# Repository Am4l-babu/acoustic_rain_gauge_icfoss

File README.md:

# 🌧️ ICFOSS Acoustic Rain Gauge

An innovative research and development project by **ICFOSS (International Centre for Free and Open Source Software, Kerala)** to estimate rainfall rate and precipitation dynamics in real-time by analyzing the **sound of raindrops** falling on a metallic enclosure using Machine Learning.

> [!NOTE]  
> Traditional rain gauges are mechanical (tipping buckets) or optical, which require high maintenance and are prone to debris clogging. The acoustic rain gauge presents a low-cost, solid-state, maintenance-free alternative.

---

## 🛠️ Hardware & Data Acquisition (DAQ) Stack

The system consists of a recording setup calibrated against a physical mechanical reference:

1.  **Acoustic Sensor**: USB Microphone (Jieli Technology UACDemoV1.0) placed inside a specialized metallic enclosure.
2.  **Data Logger**: Raspberry Pi running automated audio acquisition scripts.
3.  **Reference Sensor**: **Davis AeroCone 6466M Rain Gauge** (mechanical tipping bucket) used for continuous calibration and ground-truth labels.

---

## 📂 Project Structure

```directory
├── software/
│   ├── rainfall_monitor_nonmechanical/
│   │   ├── model_pipeline.py       # <-- End-to-end alignment & ML pipeline
│   │   ├── demo_app.py             # Streamlit visualization dashboard
│   │   ├── raindrop_counter.py     # Real-time rain drop counting script
│   │   └── requirements.txt        # Python dependencies
│   ├── Firmware/                   # LoRaWAN and Arduino firmware
│   └── hardware/                   # Circuit diagrams & CAD drawings
├── DATA/                           # Local calibration data
├── experiments/                    # Model validation records
└── README.md                       # Root documentation
```

---

## 🧠 Machine Learning Pipeline

The pipeline aligns audio files with the mechanical sensor log, extracts acoustic features, and trains regressors to estimate rainfall.

### 1. Data Alignment
Since the mechanical Davis rain gauge reports precipitation accumulated over 3-minute windows, the pipeline parses the timestamps of 3.12-second audio clips (`yyyy_mm_dd_hh_mm_ss_micro.wav`) and groups/concatenates the 18 audio clips that fall into each 3-minute reporting window.

### 2. Acoustic Feature Extraction
For each aligned 3-minute window, we extract a **264-dimensional feature vector**:
*   **Mel-Frequency Spectrogram (64 bins)**: We compute the log Mel spectrogram and extract the **Mean** and **Standard Deviation** for each bin to represent pitch profile and loudness.
*   **Zero Crossing Rate (ZCR)**: Captures the rate of waveform sign changes to identify high-frequency drop impacts.
*   **RMS Energy**: Measures average sound amplitude (physical loudness).
*   **Spectral Centroid & Rolloff**: Identifies the center of spectral mass and skewness to differentiate rain from wind or traffic noise.

### 3. Model Performance Comparison
Models are split chronologically (75% train, 25% test) to mimic real-world deployment. The results:

| Model | Test MAE (mm) | Test RMSE (mm) | Test Correlation (Pearson $r$) |
| :--- | :---: | :---: | :---: |
| **Baseline (Mean)** | 0.7713 | 1.4733 | 0.00% |
| **Random Forest** | 0.9184 | 1.8899 | **50.23%** |
| **Gradient Boosting** | 0.8822 | 1.7740 | **49.92%** |
| **Neural Network (MLP)** | 0.9654 | 1.6861 | 36.00% |

> [!TIP]
> **Random Forest** and **Gradient Boosting** are the best performing models, achieving a **~50% correlation** with actual physical tipping events, demonstrating the viability of acoustic rainfall monitoring.

---

## 🚀 Getting Started

### 📋 Prerequisites
*   Python 3.11+ (tested on Python 3.14)
*   Virtual environment manager

### 🔧 Setup & Virtualenv
1. Clone the repository and navigate to the software folder:
   ```bash
   git clone https://github.com/Am4l-babu/acoustic_rain_gauge_icfoss.git
   cd acoustic_rain_gauge_icfoss
   ```
2. Initialize virtual environment and install dependencies:
   ```bash
   python -m venv .venv
   .venv\Scripts\activate      # On Windows
   source .venv/bin/activate   # On Unix/macOS
   pip install -r software/rainfall_monitor_nonmechanical/requirements.txt
   pip install tabulate
   ```

### ⚡ Running the Pipeline
Run the model pipeline script to align datasets, cache features, and train the regressors:
```bash
python software/rainfall_monitor_nonmechanical/model_pipeline.py
```

### 🖥️ Streamlit Dashboard
Launch the visualization dashboard to view predictions and live estimation:
```bash
streamlit run software/rainfall_monitor_nonmechanical/demo_app.py
```

---

## 👤 Developer & Contributor
*   **Amal Babu** ([@Am4l-babu](https://github.com/Am4l-babu))

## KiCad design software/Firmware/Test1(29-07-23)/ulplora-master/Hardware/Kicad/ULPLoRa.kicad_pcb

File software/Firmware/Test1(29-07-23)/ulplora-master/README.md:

# ULPLoRa Project

Ultra Low Power LoRa Board repository contains software, hardware sources and documentation
## Getting Started

* Make sure that you have a ULP LoRa Board.
* Install arduino-lmic from [here](https://gitlab.com/icfoss/OpenIoT/ulplora/tree/master/Software/Arduino/Libraries/) . Copy the library to ~/Arduino/libraries/
* Select board : Arduino Pro Mini 3.3v 8Mhz
* Try Example : [ULPLoRa_ABP](https://gitlab.com/icfoss/OpenIoT/ulplora/tree/master/Software/Arduino/Examples)
   
### Prerequisites

Arduino IDE - 1.8.5 [Tested]

## Contributing

Instructions coming up soon.

## License

This project is licensed under the MIT License - see the [LICENSE.md](LICENSE.md) file for details

## Acknowledgments

* LMIC by [matthijskooijman](https://github.com/matthijskooijman/arduino-lmic)

## Changelog

* V2.1 : Removed Onboard Li-ion charging circuit. Added reverse polarity protection for RP-604. Updated battery voltage sensing circuit. Removed analog interfaces which were found to be of limited use.

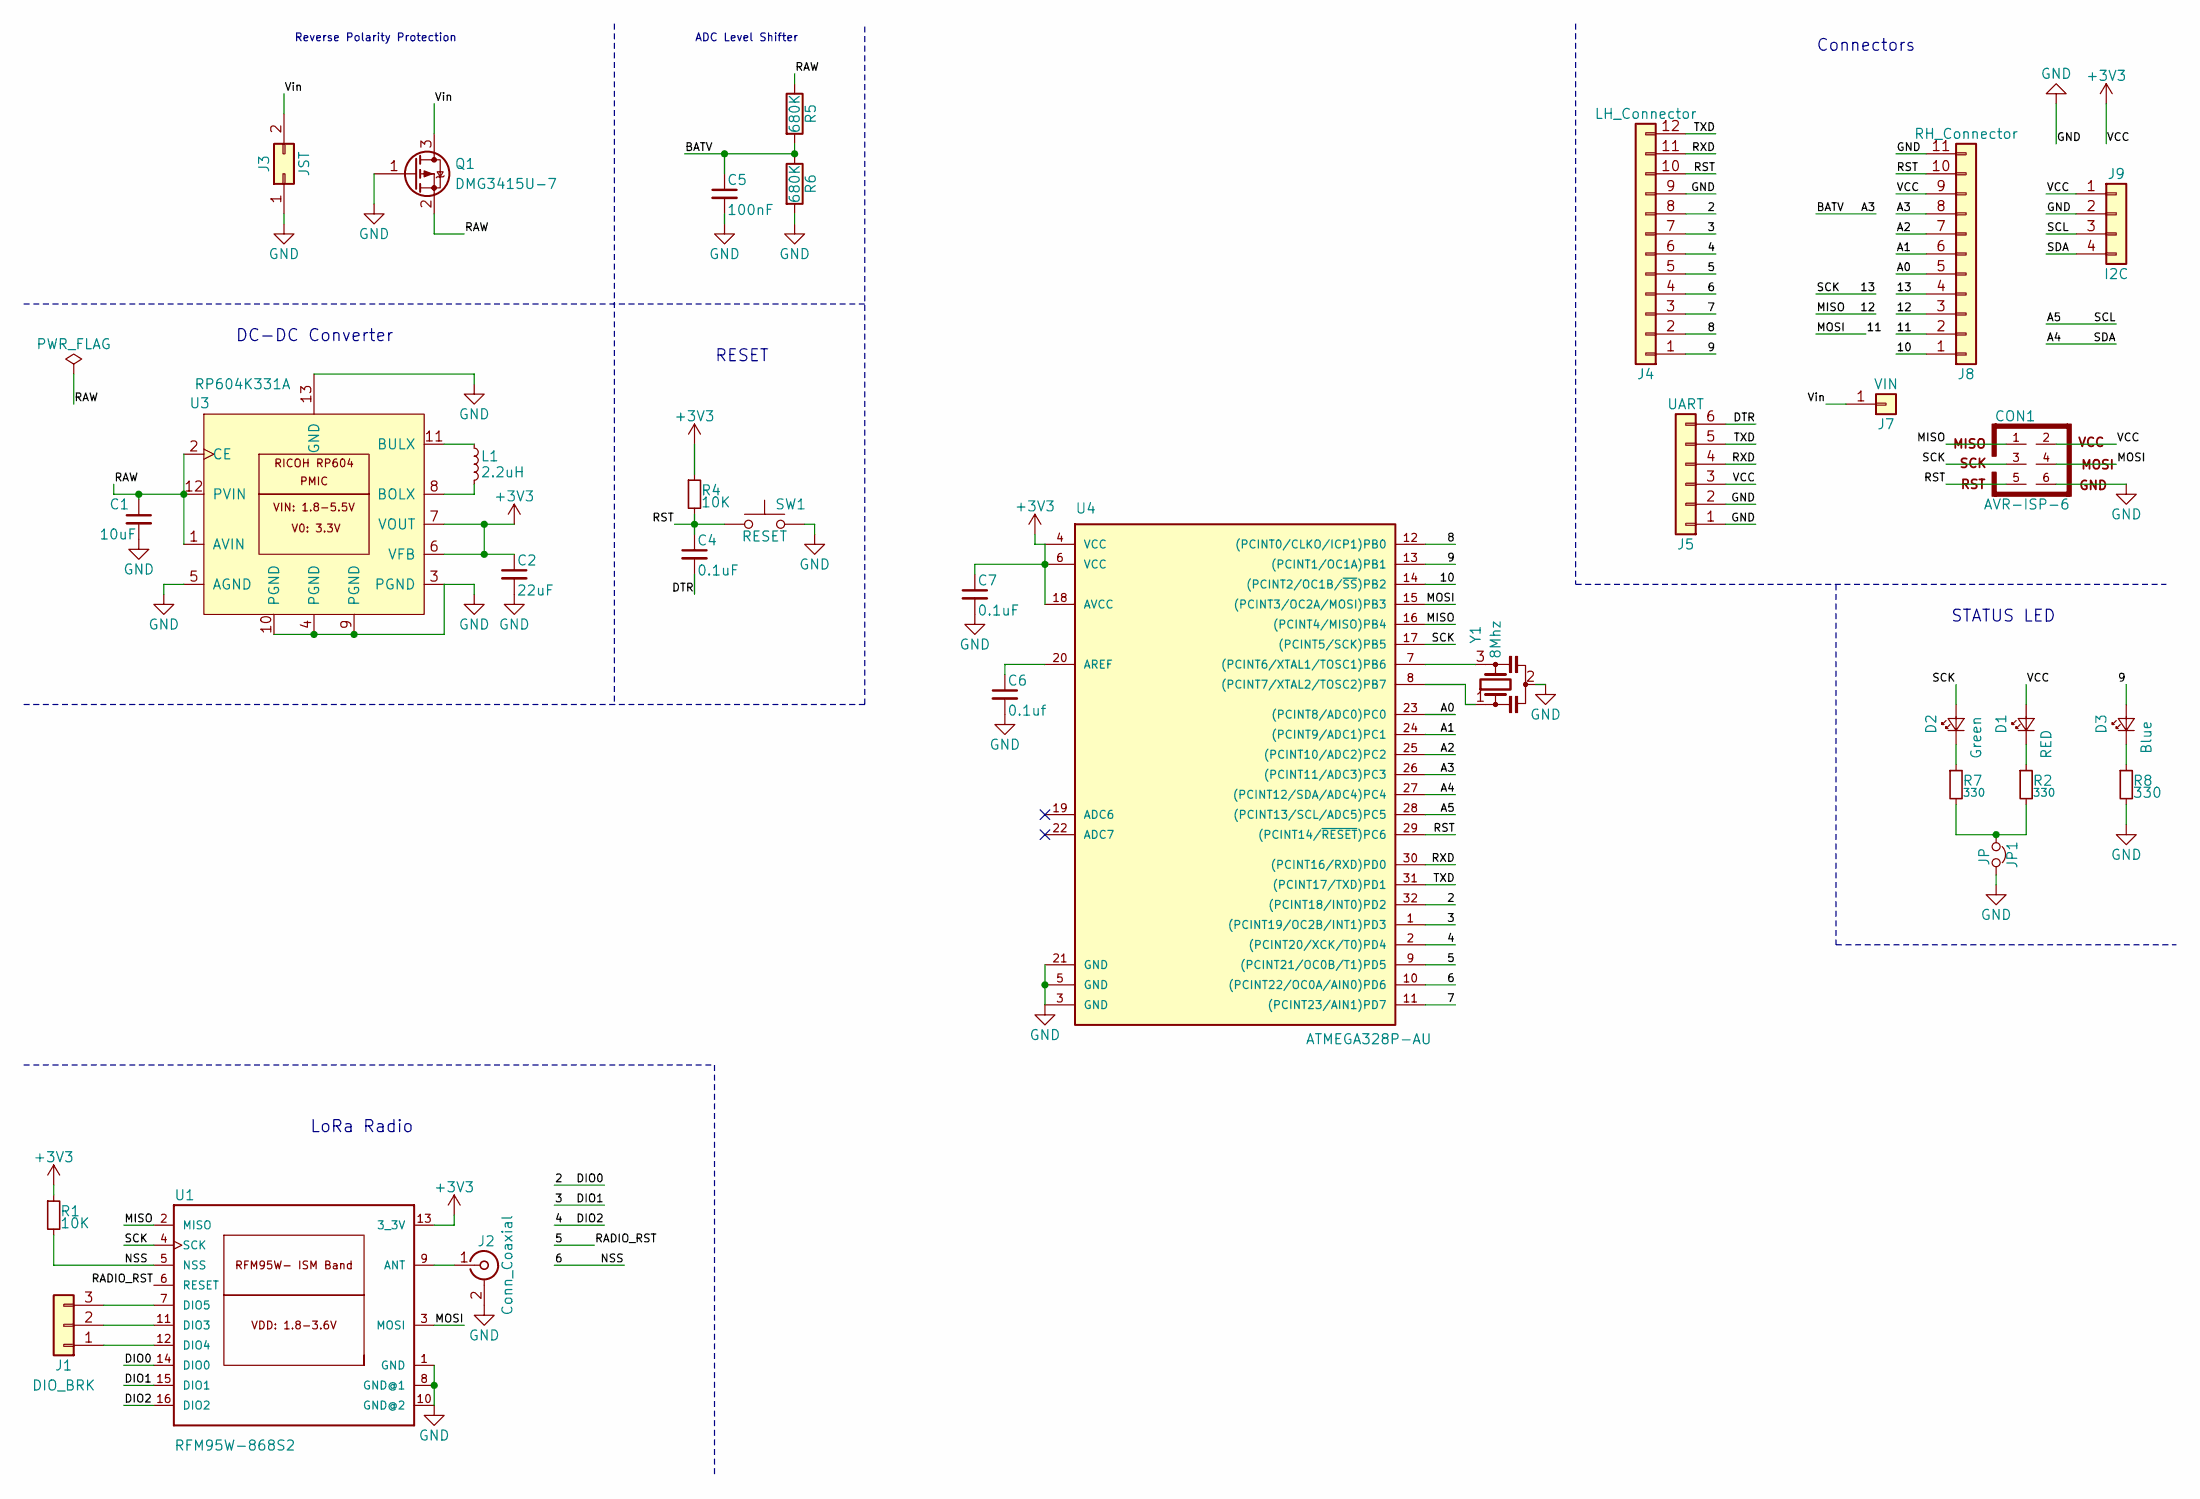
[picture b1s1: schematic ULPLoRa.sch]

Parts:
C1: 10uF; C_0805
C2: 22uF; C_0805
C4, C7: 0.1uF; C_0805
C5: 100nF; C_0805
C6: 0.1uf; C_0805
CON1: AVR-ISP-6; Pin_Header_Straight_2x03_Pitch2.54mm
D1: RED; LED_0805
D2: Green; LED_0805
D3: Blue; LED_0805
J1: DIO_BRK; Pin_Header_Straight_1x03_Pitch2.54mm
J2: Conn_Coaxial; U.FL-COAX
J3: JST; JST_PH_S2B-PH-K_02x2.00mm_Angled
J4: LH_Connector; Pin_Header_Straight_1x12_Pitch2.54mm
J5: UART; Pin_Header_Straight_1x06_Pitch2.54mm
J7: VIN; Pin_Header_Straight_1x01_Pitch2.54mm
J8: RH_Connector; Pin_Header_Straight_1x11_Pitch2.54mm
J9: I2C; JST_XH_B04B-XH-A_04x2.50mm_Straight
JP1: JP; Pin_Header_Straight_1x02_Pitch2.54mm
L1: 2.2uH; L_1210_HandSoldering
Q1: DMG3415U-7; SOT-23
R1, R4: 10K; R_0805
R2, R7, R8: 330; R_0805
R5, R6: 680K; R_0805
SW1: RESET; 3x6x2.5mm_tact_switch
U1: RFM95W-868S2; XCVR_RFM95W-868S2
U3: RP604K331A; DFN-12-1EP_2.7x3mm_Pitch0.5mm
U4: ATMEGA328P-AU; TQFP-32_7x7mm_Pitch0.8mm
Y1: 8Mhz; RESONATOR-SMD

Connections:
+3V3: C2.1, C7.1, CON1.2, D1.2 (A), J5.3, J8.9, J9.1, R1.1, R4.1, U1.13 (3_3V), U3.6 (VFB), U3.7 (VOUT), U4.4 (VCC), U4.6 (VCC), U4.18 (AVCC)
/2: J4.8, U1.14 (DIO0), U4.32 ((PCINT18/INT0)PD2)
/3: J4.7, U1.15 (DIO1), U4.1 ((PCINT19/OC2B/INT1)PD3)
/4: J4.6, U1.16 (DIO2), U4.2 ((PCINT20/XCK/T0)PD4)
/5: J4.5, U1.6 (RESET), U4.9 ((PCINT21/OC0B/T1)PD5)
/6: J4.4, R1.2, U1.5 (NSS), U4.10 ((PCINT22/OC0A/AIN0)PD6)
/7: J4.3, U4.11 ((PCINT23/AIN1)PD7)
/8: J4.2, U4.12 ((PCINT0/CLKO/ICP1)PB0)
/9: D3.2 (A), J4.1, U4.13 ((PCINT1/OC1A)PB1)
/10: J8.1, U4.14 ((PCINT2/OC1B/~SS~)PB2)
/11: CON1.4, J8.2, U1.3 (MOSI), U4.15 ((PCINT3/OC2A/MOSI)PB3)
/12: CON1.1, J8.3, U1.2 (MISO), U4.16 ((PCINT4/MISO)PB4)
/13: CON1.3, D2.2 (A), J8.4, U1.4 (SCK), U4.17 ((PCINT5/SCK)PB5)
/A0: J8.5, U4.23 ((PCINT8/ADC0)PC0)
/A1: J8.6, U4.24 ((PCINT9/ADC1)PC1)
/A2: J8.7, U4.25 ((PCINT10/ADC2)PC2)
/A3: C5.1, J8.8, R5.2, R6.1, U4.26 ((PCINT11/ADC3)PC3)
/A4: J9.4, U4.27 ((PCINT12/SDA/ADC4)PC4)
/A5: J9.3, U4.28 ((PCINT13/SCL/ADC5)PC5)
/A6: U4.19 (ADC6)
/A7: U4.22 (ADC7)
/DTR: C4.2, J5.6
/RAW: C1.1, Q1.2 (S), R5.1, U3.1 (AVIN), U3.2 (CE), U3.12 (PVIN)
/RST: C4.1, CON1.5, J4.10, J8.10, R4.2, SW1.1, U4.29 ((PCINT14/~RESET~)PC6)
/RXD: J4.11, J5.4, U4.30 ((PCINT16/RXD)PD0)
/TXD: J4.12, J5.5, U4.31 ((PCINT17/TXD)PD1)
/Vin: J3.2, J7.1, Q1.3 (D)
GND: C1.2, C2.2, C5.2, C6.2, C7.2, CON1.6, J2.2 (Ext), J3.1, J4.9, J5.1, J5.2, J8.11, J9.2, JP1.2, Q1.1 (G), R6.2, R8.2, SW1.2, U1.1 (GND), U1.8 (GND@1), U1.10 (GND@2), U3.3 (PGND), U3.4 (PGND), U3.5 (AGND), U3.9 (PGND), U3.10 (PGND), U3.13 (GND), U4.3 (GND), U4.5 (GND), U4.21 (GND), Y1.2
unnamed: C6.1, U4.20 (AREF)
unnamed: D1.1 (K), R2.1
unnamed: D2.1 (K), R7.1
unnamed: D3.1 (K), R8.1
unnamed: J1.1, U1.12 (DIO4)
unnamed: J1.2, U1.11 (DIO3)
unnamed: J1.3, U1.7 (DIO5)
unnamed: J2.1 (In), U1.9 (ANT)
unnamed: JP1.1, R2.2, R7.2
unnamed: L1.1, U3.11 (BULX)
unnamed: L1.2, U3.8 (BOLX)
unnamed: U4.7 ((PCINT6/XTAL1/TOSC1)PB6), Y1.3
unnamed: U4.8 ((PCINT7/XTAL2/TOSC2)PB7), Y1.1

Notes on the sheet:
LoRa Radio
DC-DC Converter
RESET
Connectors
STATUS LED
Reverse Polarity Protection
ADC Level Shifter

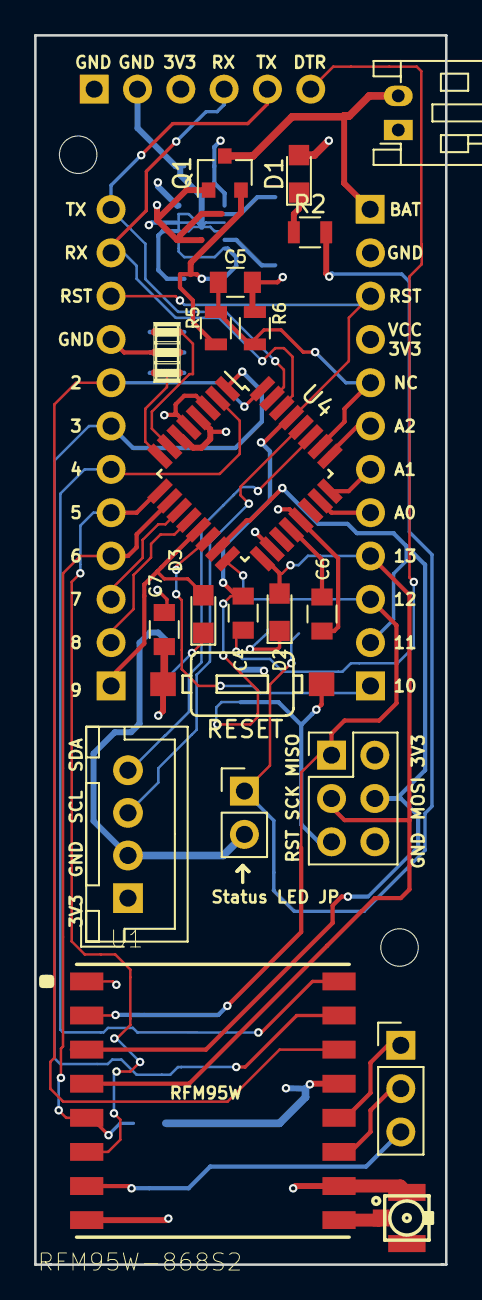
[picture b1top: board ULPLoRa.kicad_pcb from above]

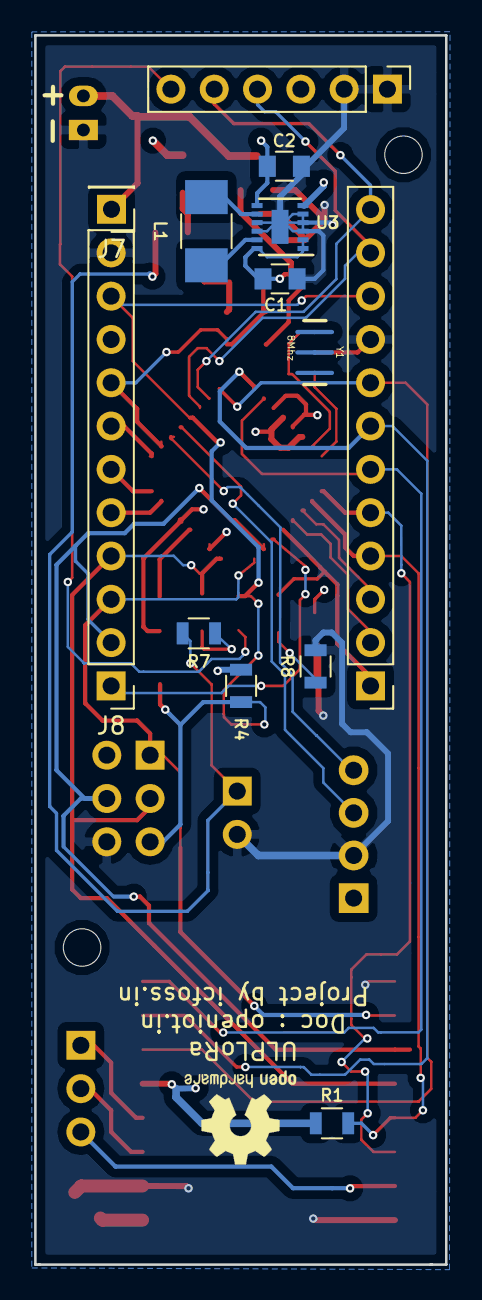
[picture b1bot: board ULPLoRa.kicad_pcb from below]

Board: 4 copper layers, 24.1 x 72.1 mm, 33 parts (12 on the bottom side), 39 nets.

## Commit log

2026-06-08 Initial commit: ICFOSS Acoustic Rain Gauge - complete project with firmware, ML pipeline, data, hardware docs, and literature
2026-06-15 Add machine learning model training and evaluation pipeline
2026-06-15 Clean repository: keep essential files, update README and ignore lists
2026-06-15 Optimize acoustic rain gauge model with tuned target log-transform and SVR

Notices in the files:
README.md:
License: MIT
